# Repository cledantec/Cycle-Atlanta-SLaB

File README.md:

Cycle Atlanta: Seeing Like a Bike
================
[Atlanta's Data Science for Social Good (DSSG) 2017](http://dssg-atl.io/)
----------

The Cycle Atlanta project aims to create sensor systems that allow a bike to "see" its environment and collect data as a participatory effort to help the City of Atlanta make informed decisions about biking infrastructures. The team from Atlanta's Data Science for Social Good 2017 Summer program particularly worked on (1) reverse engineering all the prototypes developed separately by the LMC6650 team and consolidating all sensors into two microcontoller units (Raspberry Pi and Arduino) using the Master-Slave architecture; (2) identifying hardware/software bugs/flaws and refining systems iteratively; (3) implementing failure-tolerence techniques; (4) classifying environmental factors (to detect semantci-level objects) after collecting data using GoPro, voice recorders, and sensors; and (5) visualizing and analyzing the collected data using 3D models and machine learning techniques. 

## Documentations
* [System Overview](DSSG2017_doc/overview.md)
* [Hardware Systems (Electrical Devices and Circuits)](DSSG2017_doc/hardware.md)
* [Software Systems (Server Configurations and Scripts)](DSSG2017_doc/software.md)
* [Cases Design](DSSG2017_doc/cases.md)
* [Data Visualization (3D)](DSSG2017_doc/dataviz.md)
* [Data Analysis](DSSG2017_doc/data.md)
* [Backlog (Issues and Solutions)](DSSG2017_doc/backlog.md)

## Credits (DSSG)
### PI:
* [Dr. Christopher Le Dantec](https://ledantec.net/)

### DSSG Fellows:
* [Javier Argota](http://jard.us)
* [Myeong Lee](http://myeonglee.com)
* [Noel Mannariat](mailto:noelmannariat@gmail.com)
* [Erica Pantoja](mailto:ericapantoja1190@gmail.com)

### Special Thanks To:
* Dr. Kari Watkins
* Mariam Asad
* Bijan Tehrani
* Raj Lal
* Michael Vogel
* Bradley Rittenhouse

******

## [LMC6650: Seeing Like a Bike](http://ledantec.net/teaching/lmc-6650-spring-2017/)
### Spring 2017 Georgia Tech

LMC6650 students designed a custom PCB board for gas sensors, developed the Air Quality module and a data collection server on Raspberry Pi using RestAPIs, and implemented the proximity/serface quality sensor functionalities using Rapsberry Pi and Arduino. 

## Equipment used
* [Raspberry Pi](http://raspberrypi.org)
* [Arduino Uno](https://www.arduino.cc/en/Main/arduinoBoardUno)
* [Matrix One Creator](http://creator.matrix.one)
* [Anker 26800 mAh portable power bank](https://www.amazon.com/Anker-PowerCore-Portable-Double-Speed-Recharging/dp/B01JIWQPMW)
* [Knowles BU21771 contact microphone](www.digikey.com/product-detail/en/knowles/BU-21771-000/423-1004-ND/458515)
* Dimension ST768 for 3D printing

## Credits (LMC6650)
* **Air Quality team**: [Orianna Ott](https://www.linkedin.com/in/orianaott/) , [Lorina Navarro](https://www.linkedin.com/in/lmnavarro/) , [Reuben Fishback](https://www.linkedin.com/in/reuben-fishback-a4b31085/)
* **Proximity team**: [Sharon Ang](https://www.linkedin.com/in/sharon-ang/) , [Aastha Jalan](https://www.linkedin.com/in/aasthajalan/) , [Nikhil Soraba](https://www.linkedin.com/in/nikhil-soraba/)
* **Surface Quality team**: [Nene Igietseme](https://www.linkedin.com/in/nene-igietseme-19b65125/) , [Kristin Hare](https://www.linkedin.com/in/kristin-hare/) , [Shruti Dalvi](https://www.linkedin.com/in/shruti-dalvi/) , [Jayanth Mohana Krishna](https://linkedin.com/in/jayanthm)

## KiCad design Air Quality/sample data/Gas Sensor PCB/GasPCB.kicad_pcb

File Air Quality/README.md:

# Air Quality & GPS Sensor readme

Code for running air quality and GPS sensors. 

Installation 
============

Copy all files in the RaspberryPi directory to the home directory of the Raspberry Pi.
Install the Adafruit Python DHT and ADS1x15 libraries in the 'dependencies' directory (see README there for details—you will need an active network connection to install their dependencies).

To run:

```
sudo python ~/air_quaility/aq_init.py
```
To autorun, edit the ~/.config/lxsession/LXDE-pi/autostart file by adding:

```
@python /home/pi/airquality/aq_init.py
```

Old Code
--------
Located in the 'unused' directory, these source files aren't used or were renamed for production.

*AirMaster.py*
Contains all the relevant code from the other three python scripts.
It also connects to the server and sends JSON data every 4-5 seconds.

The following three files are test scripts
Once each was working the code was added to AirMaster.py

*USBserial.py*
This script will initialize and read from the USB port.

*serial_read.py* 
This script will read from the GPS that is connected to the tx and rx 
lines. It also isolates the desirable data and parses it out.

*i2c.py*
This code will use the Adafruit Python DHT library to read i2c.
It will also scale the values in an attempt to convert them to ppm.

*DustSensor.ino* 
This is arduino code that runs on the teensy arduino.
Reads analog value from PM sensor every second and sends over USB

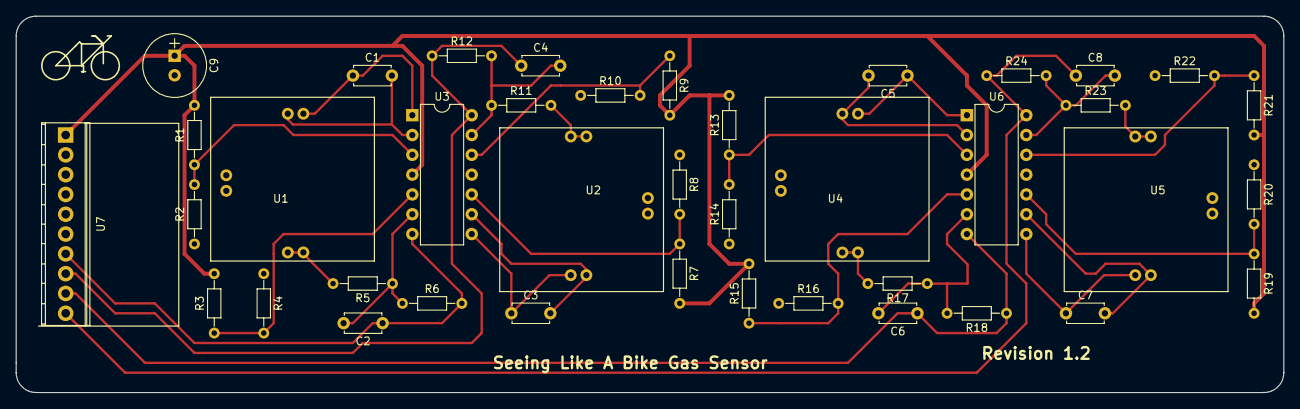
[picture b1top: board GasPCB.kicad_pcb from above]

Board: 2 copper layers, 162.6 x 48.3 mm, 40 parts (0 on the bottom side), 30 nets.

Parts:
C1, C2, C3, C4, C5, C6, C7, C8: 0.1uF; C_Disc_D4.7mm_W2.5mm_P5.00mm
C9: 10uF; CP_Radial_Tantal_D8.0mm_P2.50mm
R1, R2, R3, R4, R6, R7, R8, R9, R10, R12, R13, R14, R15, R16, R18, R19, R20, R21, R22, R24: R; R_Axial_DIN0204_L3.6mm_D1.6mm_P7.62mm_Horizontal
R5, R11, R17, R23: 150; R_Axial_DIN0204_L3.6mm_D1.6mm_P7.62mm_Horizontal
U1, U2, U4, U5: GasSensor
U3, U6: LF347N; DIP-14_W7.62mm
U7: ADS1015; TerminalBlock_Pheonix_MPT-2.54mm_10pol

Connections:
GND: C9.2, R2.1, R4.1, R8.1, R10.1, R14.1, R16.1, R20.1, R22.1, U3.11, U6.11, U7.2
unnamed: C1.1, U1.5, U3.1
unnamed: C1.2, U1.4, U3.2
unnamed: C2.2, R5.1, R6.1, U3.6
unnamed: C3.1, U2.5, U3.8
unnamed: C3.2, U2.4, U3.9
unnamed: C4.2, R11.1, R12.2, U3.13
unnamed: C5.1, U4.5, U6.1
unnamed: C5.2, U4.4, U6.2
unnamed: C6.2, R17.1, R18.2, U6.6
unnamed: C7.1, U5.5, U6.8
unnamed: C7.2, U5.4, U6.9
unnamed: C8.2, R23.1, R24.2, U6.13
unnamed: R1.1, R2.2, U3.3
unnamed: R3.1, R4.2, U3.5
unnamed: R5.2, U1.1, U1.6
unnamed: R7.1, R8.2, U3.10
unnamed: R9.1, R10.2, U3.12
unnamed: R11.2, U2.1, U2.6
unnamed: R13.1, R14.2, U6.3
unnamed: R15.1, R16.2, U6.5
unnamed: R17.2, U4.1, U4.6
unnamed: R19.1, R20.2, U6.10
unnamed: R21.1, R22.2, U6.12
unnamed: R23.2, U5.1, U5.6
V+: C9.1, R1.2, R3.2, R7.2, R9.2, R13.2, R15.2, R19.2, R21.2, U3.4, U6.4, U7.1
VOUT0: C2.1, R6.2, U3.7, U7.7
VOUT1: C4.1, R12.1, U3.14, U7.8
VOUT2: C6.1, R18.1, U6.7, U7.9
VOUT3: C8.1, R24.1, U6.14, U7.10

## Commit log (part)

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2017-04-22 Surface quality initial commit - package.json has all the Node modules needed - *_server.js scripts are NodeJS clients that send the server data - added data cleanup script, output CSV, tableau analy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
2017-04-22 Air Quality initial commit
2017-04-22 Added more images GoPro straight mount STL
2017-04-22 readme.md changes
2017-04-23 Added comments to server code
2017-04-24 Added opencv code to surface
2017-04-24 Added Air Quality endpoints
2017-04-24 Proximity files
    All the source code used by the proximity team to collect data from
    ultrasound and lidar sensors.
2017-04-26 Server documentation uploaded
2017-05-17 Adjusted error message & updated readme
2017-05-25 Re-org
    Major reorg of each component. Re-writing code for AQ.
2017-05-25 .DS_Store banished!
2017-05-25 Remove .idea
2017-05-31 Python scripts that operate sensors on the Matrix board
2017-06-09 Add files via upload
    Code for gps using USB
2017-06-12 changes in Arduino files
2017-06-12 added distance0 and libraries
2017-06-12 new server files
2017-06-12 arduino file updated
2017-06-14 Sensor receiver added
2017-06-15 LED enabled. Serial communication refined
2017-06-16 GPS and Sensors work together (+ LEDs)
2017-06-16 LED complete. All sensors work together fine. Sensor resolution adjusted
2017-06-20 styling
2017-06-27 Reset functionality implemented in Raspberry Pi and Arduion. Sync issue resolved. USB ports fixed for serial communications
2017-06-27 time interval to 0.1 sec
2017-06-27 sample 10 min data
2017-06-27 removed Null values
2017-06-28 descriptive graphs
2017-06-28 stamen map added
2017-07-07 Gas sensor testbed added
2017-07-07 a new gas calibration data
2017-07-11 gas boards 4,5,7 added
2017-07-11 R script added
2017-07-12 gas sensor graphs
2017-07-13 Mariam's test ruriding data
2017-07-14 Gas station data added
2017-07-15 Time-series speed graph
2017-07-18 some code inhancement and signautre data
2017-07-18 Arduino sync issue resolved
2017-07-18 parameter changed. official gas station data added
2017-07-18 re-indexing
2017-07-18 sidewalk riding data added
2017-07-18 Jeremy's recent data
2017-07-18 CO and SO2 added
2017-07-19 data order
2017-07-19 Signature data with corrected sonar sensors
2017-07-20 added 0719 riding for signatures
2017-07-20 signature examples
2017-07-20 proximity data updated for 0719
2017-07-20 new data and signatures
2017-07-21 graphs and new sig data
2017-07-21 Mariam's 0720 dataata
2017-07-21 Jeremy's 0721 data
2017-07-21 gas aggregated to 0718 data
2017-07-21 Prox and GPS joined for Jeremy's 0721:
2017-07-21 Signatures
2017-07-22 gas calibration graphs
2017-07-22 Mariam's 0720 joined data
2017-07-22 Create All_Graphs
2017-07-22 Create akk
2017-07-22 Javier's 0722
2017-07-22 0722 Javier's Join table
2017-07-22 A folder deleted
2017-07-22 Updated Signatures
2017-07-22 Use These (Updated)
2017-07-22 deleted unnecessary files
2017-07-22 0722 Signatures Added
2017-07-22 deleted a folder
2017-07-22 0722 Signatures
2017-07-23 Create 2207_SignaturesErica
2017-07-23 Same route data on 0723
2017-07-23 Create files
2017-07-23 distance-based data
2017-07-23 csv clean up
2017-07-23 gps proximity joined for the same route riding 0722
2017-07-23 change of locations
2017-07-23 distance-based resampling
2017-07-24 Signature
2017-07-24 first part of 0722, resampled for all variables
2017-07-24 random classifires added for testing
2017-07-24 random classifiers for both sides
2017-07-24 day-time added
2017-07-24 classification data
2017-07-24 classifications
2017-07-24 data processing graphs
2017-07-25 Readme for the front page
2017-07-25 typo
2017-07-25 modifications in MD
2017-07-25 fixed links
2017-07-25 removed blank
2017-07-25 mailto
2017-07-26 Doc skeletons
2017-07-26 docs..
2017-07-26 MD link corrected
2017-07-26 viz doc added
2017-07-26 added Myeong's name
2017-07-26 test mod
2017-07-26 added Noel's name
2017-07-26 added Erica's name
2017-07-26 matrix image
2017-07-26 basic viz page
2017-07-26 basic viz page information 2
2017-07-27 system overview
2017-07-27 classifiers data
2017-07-27 data analysis draft
2017-07-27 formatting
2017-07-27 Rhino folder added and Grasshopper definition + viz webpage update
2017-07-27 viz webpage updating
2017-07-27 viz webpage update + gh file update
2017-07-27 hardware agenda
2017-07-27 gps image
2017-07-27 gpsStructure image
2017-07-27 gasSensor Image
2017-07-27 data analysis
2017-07-27 image path corrected
2017-07-28 sensorInfo
2017-07-28 imgs and folders for PCB
2017-07-28 folders for ABS box + doc for back box
2017-07-28 create ABS boxes md file
2017-07-28 Rename ABS_laser_cutting to ABS_laser_cutting.md
2017-07-28 gpsStructure_Image
2017-07-28 Rename ABS_laser_cutting.md to README.md
2017-07-28 update README back box
2017-07-28 hardware update
2017-07-28 adding PCB image
2017-07-28 software doc addoc added. John's data added
2017-07-28 Added Case folder
2017-07-28 Added images
2017-07-28 Added Case doc
2017-07-28 gas documentation
2017-07-28 doc first draft
2017-07-28 links
2017-09-22 fixing youtube video link on hardware page
2018-08-22 Adding code from Summer 2018
2018-08-22 Added readme for CDS 2018
2019-05-03 All Scripts Created Fall 18 - Spring 19
    All of the scripts created from Fall 2018 to Spring 2019 are included along with a readme that explains how to run them and what they are for.
2020-04-12 TheWoodruffGroup Capstone Android App
2020-04-13 Create README.md
    Documentation for Spring 2020 Capstone project for The Woodruff Group
2020-04-14 Edited package name
2020-04-14 Enlarged button text size
2020-04-14 Updated contact info
2020-04-15 Changed folder structure
2020-04-15 Added mechanical and electrical documentation files
2020-04-15 Added Bluetooth test app
2020-04-24 Added electrical files and documentation
2020-04-24 Fixed electrical documentation formatting
2020-04-30 feat: add wjmy
2020-05-02 Bump acorn from 6.4.0 to 6.4.1 in /SLAB-wjmy/wjmy-app
    Bumps [acorn](https://github.com/acornjs/acorn) from 6.4.0 to 6.4.1.
    - [Release notes](https://github.com/acornjs/acorn/releases)
    - [Commits](https://github.com/acornjs/acorn/compare/6.4.0...6.4.1)
2020-07-20 Bump lodash from 4.17.15 to 4.17.19 in /SLAB-wjmy/wjmy-app
    Bumps [lodash](https://github.com/lodash/lodash) from 4.17.15 to 4.17.19.
    - [Release notes](https://github.com/lodash/lodash/releases)
    - [Commits](https://github.com/lodash/lodash/compare/4.17.15...4.17.19)
2021-03-31 Bump y18n from 3.2.1 to 3.2.2 in /SLAB-wjmy/wjmy-app
    Bumps [y18n](https://github.com/yargs/y18n) from 3.2.1 to 3.2.2.
    - [Release notes](https://github.com/yargs/y18n/releases)
    - [Changelog](https://github.com/yargs/y18n/blob/master/CHANGELOG.md)
    - [Commits](https://github.com/yargs/y18n/commits)
2021-05-07 Bump ua-parser-js from 0.7.21 to 0.7.28 in /SLAB-wjmy/wjmy-app
    Bumps [ua-parser-js](https://github.com/faisalman/ua-parser-js) from 0.7.21 to 0.7.28.
    - [Release notes](https://github.com/faisalman/ua-parser-js/releases)
    - [Commits](https://github.com/faisalman/ua-parser-js/compare/0.7.21...0.7.28)
2021-05-11 Bump lodash from 4.17.15 to 4.17.21 in /SLAB-wjmy/wjmy-app
    Bumps [lodash](https://github.com/lodash/lodash) from 4.17.15 to 4.17.21.
    - [Release notes](https://github.com/lodash/lodash/releases)
    - [Commits](https://github.com/lodash/lodash/compare/4.17.15...4.17.21)
2021-05-11 Bump hosted-git-info from 2.8.5 to 2.8.9 in /SLAB-wjmy/wjmy-app
    Bumps [hosted-git-info](https://github.com/npm/hosted-git-info) from 2.8.5 to 2.8.9.
    - [Release notes](https://github.com/npm/hosted-git-info/releases)
    - [Changelog](https://github.com/npm/hosted-git-info/blob/v2.8.9/CHANGELOG.md)
    - [Commits](https://github.com/npm/hosted-git-info/compare/v2.8.5...v2.8.9)
2021-06-11 Bump glob-parent from 5.1.0 to 5.1.2 in /SLAB-wjmy/wjmy-app
    Bumps [glob-parent](https://github.com/gulpjs/glob-parent) from 5.1.0 to 5.1.2.
    - [Release notes](https://github.com/gulpjs/glob-parent/releases)
    - [Changelog](https://github.com/gulpjs/glob-parent/blob/main/CHANGELOG.md)
    - [Commits](https://github.com/gulpjs/glob-parent/compare/v5.1.0...v5.1.2)
    ---
    updated-dependencies:
2021-08-12 Bump path-parse from 1.0.6 to 1.0.7 in /SLAB-wjmy/wjmy-app
    Bumps [path-parse](https://github.com/jbgutierrez/path-parse) from 1.0.6 to 1.0.7.
    - [Release notes](https://github.com/jbgutierrez/path-parse/releases)
    - [Commits](https://github.com/jbgutierrez/path-parse/commits/v1.0.7)
    ---
    updated-dependencies:
    - dependency-name: path-parse
2021-09-21 Bump tmpl from 1.0.4 to 1.0.5 in /SLAB-wjmy/wjmy-app
    Bumps [tmpl](https://github.com/daaku/nodejs-tmpl) from 1.0.4 to 1.0.5.
    - [Release notes](https://github.com/daaku/nodejs-tmpl/releases)
    - [Commits](https://github.com/daaku/nodejs-tmpl/commits/v1.0.5)
    ---
    updated-dependencies:
    - dependency-name: tmpl
2022-02-13 Bump ajv from 6.11.0 to 6.12.6 in /SLAB-wjmy/wjmy-app
    Bumps [ajv](https://github.com/ajv-validator/ajv) from 6.11.0 to 6.12.6.
    - [Release notes](https://github.com/ajv-validator/ajv/releases)
    - [Commits](https://github.com/ajv-validator/ajv/compare/v6.11.0...v6.12.6)
    ---
    updated-dependencies:
    - dependency-name: ajv
2022-03-02 Bump plist from 3.0.1 to 3.0.4 in /SLAB-wjmy/wjmy-app
    Bumps [plist](https://github.com/TooTallNate/node-plist) from 3.0.1 to 3.0.4.
    - [Release notes](https://github.com/TooTallNate/node-plist/releases)
    - [Changelog](https://github.com/TooTallNate/plist.js/blob/master/History.md)
    - [Commits](https://github.com/TooTallNate/node-plist/commits)
    ---
    updated-dependencies:
2022-04-29 Bump async from 2.6.3 to 2.6.4 in /SLAB-wjmy/wjmy-app
    Bumps [async](https://github.com/caolan/async) from 2.6.3 to 2.6.4.
    - [Release notes](https://github.com/caolan/async/releases)
    - [Changelog](https://github.com/caolan/async/blob/v2.6.4/CHANGELOG.md)
    - [Commits](https://github.com/caolan/async/compare/v2.6.3...v2.6.4)
    ---
    updated-dependencies:
2022-06-02 Bump simple-plist from 1.1.0 to 1.3.1 in /SLAB-wjmy/wjmy-app
    Bumps [simple-plist](https://github.com/wollardj/simple-plist) from 1.1.0 to 1.3.1.
    - [Release notes](https://github.com/wollardj/simple-plist/releases)
    - [Commits](https://github.com/wollardj/simple-plist/compare/1.1.0...v1.3.1)
    ---
    updated-dependencies:
    - dependency-name: simple-plist
2022-10-12 Bump xmldom and plist in /SLAB-wjmy/wjmy-app
    Removes [xmldom](https://github.com/xmldom/xmldom). It's no longer used after updating ancestor dependency [plist](https://github.com/TooTallNate/node-plist). These dependencies need to be updated to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
    Removes `xmldom`
    Updates `plist` from 3.0.1 to 3.0.6
    - [Release notes](https://github.com/TooTallNate/node-plist/releases)
    - [Changelog](https://github.com/TooTallNate/plist.js/blob/master/History.md)
    - [Commits](https://github.com/TooTallNate/node-plist/commits)
2022-10-20 Bump react-native-reanimated from 1.7.0 to 2.10.0 in /SLAB-wjmy/wjmy-app
    Bumps [react-native-reanimated](https://github.com/software-mansion/react-native-reanimated) from 1.7.0 to 2.10.0.
    - [Release notes](https://github.com/software-mansion/react-native-reanimated/releases)
    - [Commits](https://github.com/software-mansion/react-native-reanimated/compare/1.7.0...2.10.0)
    ---
    updated-dependencies:
    - dependency-name: react-native-reanimated
2022-12-11 Bump qs from 6.9.1 to 6.9.7 in /SLAB-wjmy/wjmy-app
    Bumps [qs](https://github.com/ljharb/qs) from 6.9.1 to 6.9.7.
    - [Release notes](https://github.com/ljharb/qs/releases)
    - [Changelog](https://github.com/ljharb/qs/blob/main/CHANGELOG.md)
    - [Commits](https://github.com/ljharb/qs/compare/v6.9.1...v6.9.7)
    ---
    updated-dependencies:
